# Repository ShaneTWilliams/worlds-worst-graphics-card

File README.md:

# World's Worst Graphics Card

This board consists of an SiI1136 HDMI transmitter, driven by a dual-core 480 MHz STM32H745IIT6 microcontroller, with 64 MB of external SDRAM. It is USB-powered and uses SWD for flash and debug.

The goal of this project is to give me a custom, bare-metal platform on which I can try my hand at implementing simple graphics algorithms from scratch. The STM32 is key for this, with its dual cores, DMA2D (a DMA peripheral designed to fill frame buffers very quickly) and its LTDC peripheral, which will drive the display without any CPU load.

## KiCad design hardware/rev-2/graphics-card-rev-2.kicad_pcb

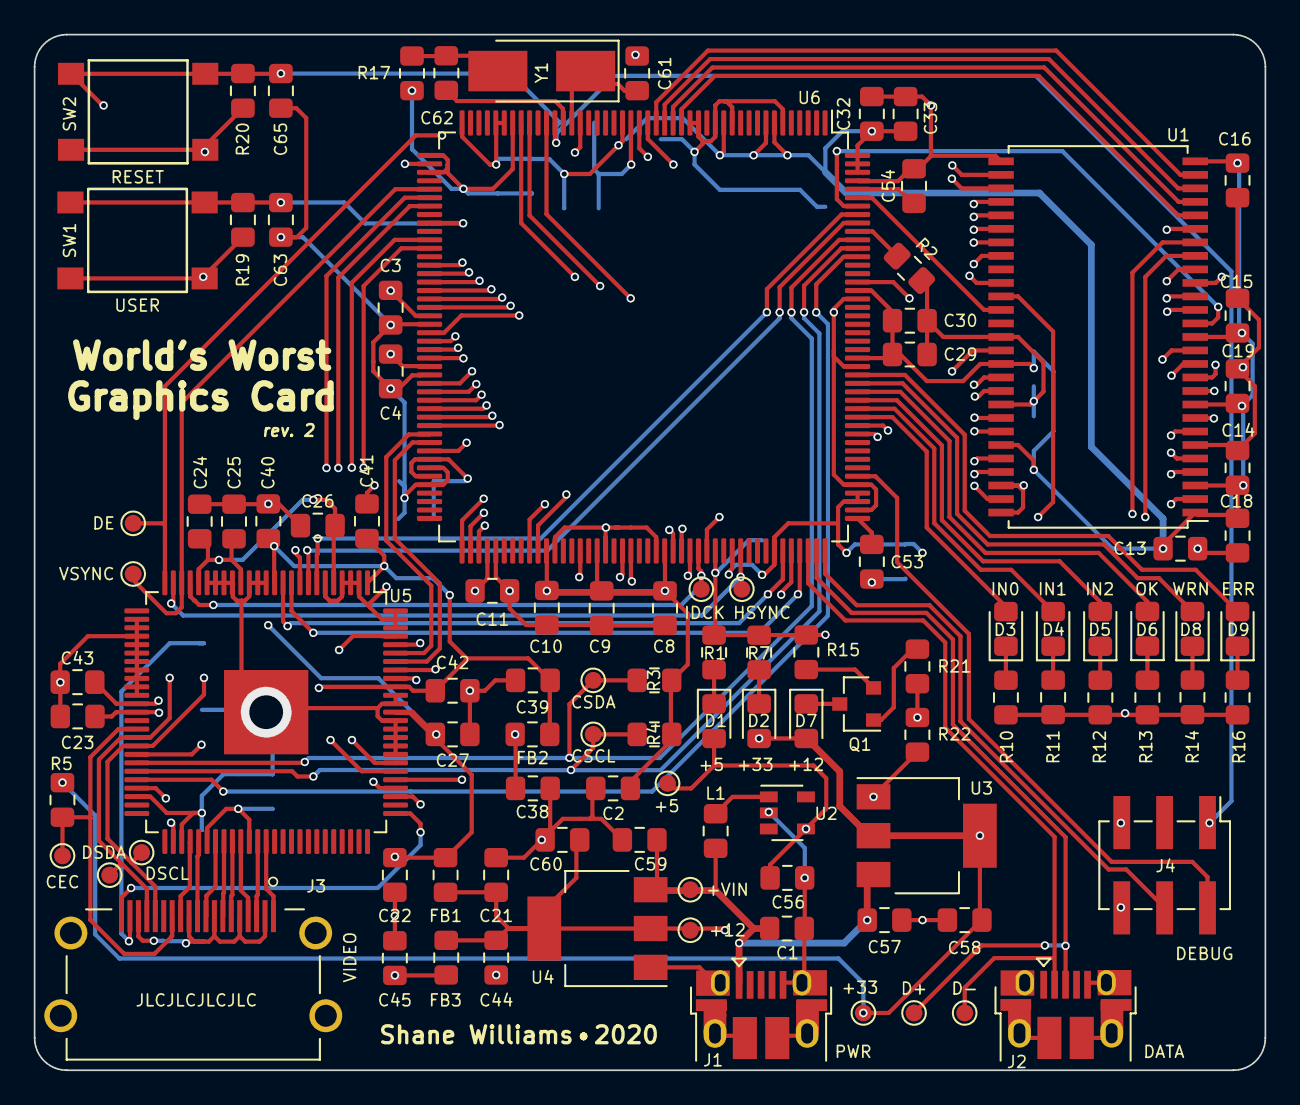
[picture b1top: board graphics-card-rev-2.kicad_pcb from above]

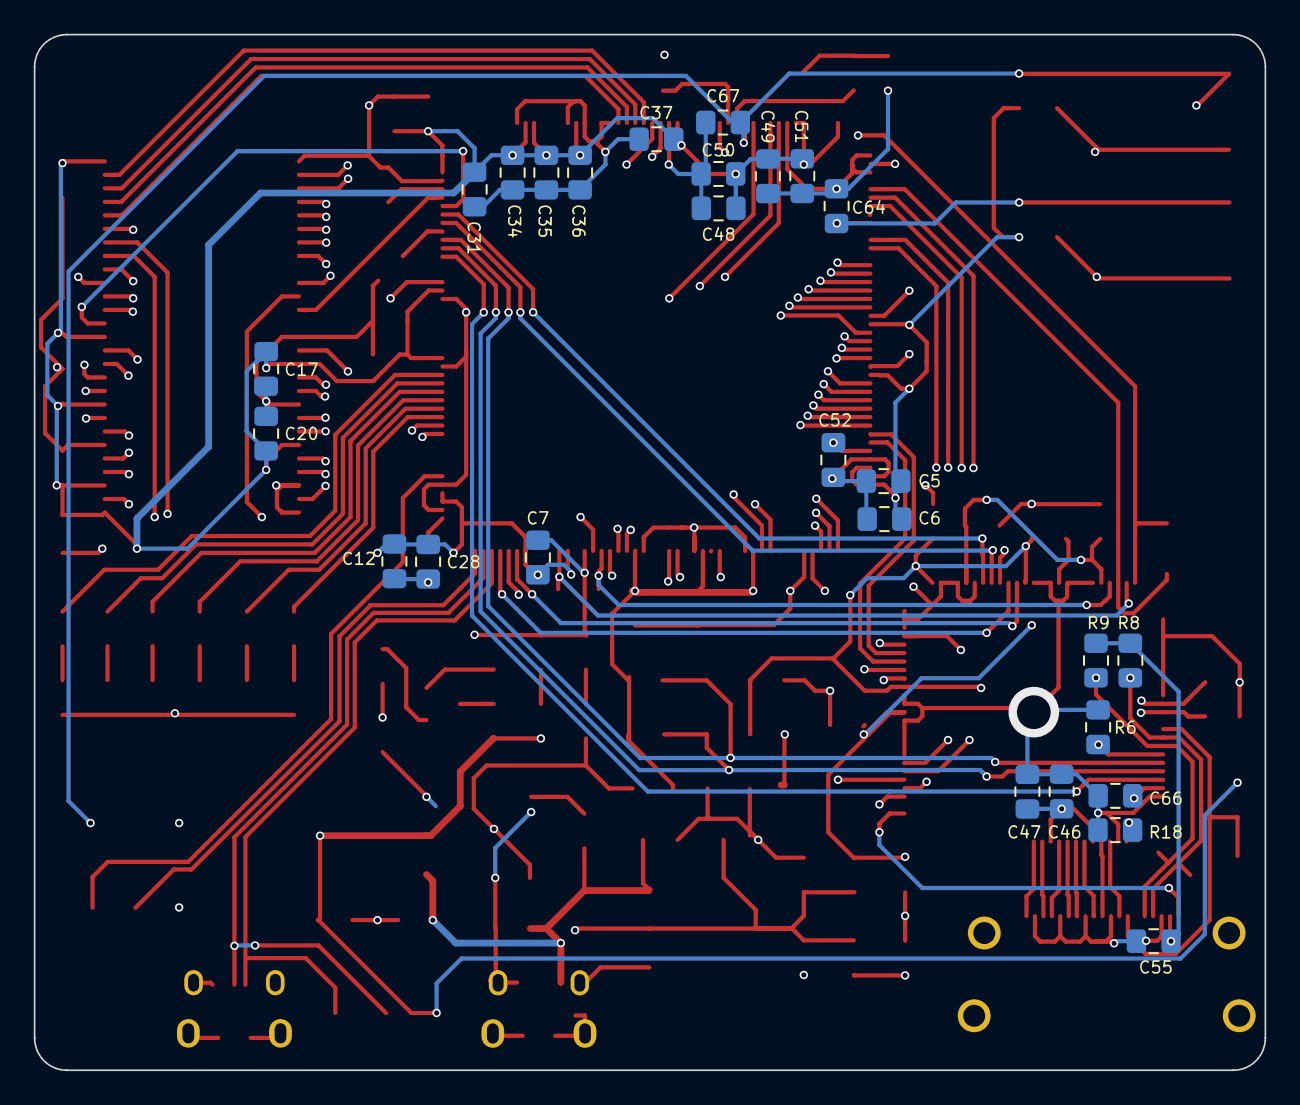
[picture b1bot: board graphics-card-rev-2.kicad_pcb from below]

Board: 4 copper layers, 72.9 x 61.3 mm, 131 parts (27 on the bottom side), 114 nets.

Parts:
+5: +5V; TestPoint_Pad_D1.0mm
+12: +1V2; TestPoint_Pad_D1.0mm
+33: +3V3; TestPoint_Pad_D1.0mm
+VIN: USB_VIN; TestPoint_Pad_D1.0mm
C1, C48, C50: 1u; C_0805_2012Metric_Pad1.15x1.40mm_HandSolder
C2, C13, C57, C58, C59, C60: 4.7u; C_0805_2012Metric_Pad1.15x1.40mm_HandSolder
C3, C4, C5, C6, C7, C8, C9, C10, C11, C12, C14, C15, C16, C17, C18, C19, C20, C21, C23, C24, C25, C26, C27, C28, C29, C30, C31, C32, C33, C34, C35, C36, C37, C38, C40, C41, C42, C43, C44, C46, C47, C49, C51, C55, C63, C64, C65, C66, C67: 100n; C_0805_2012Metric_Pad1.15x1.40mm_HandSolder
C22, C39, C45: 10u; C_0805_2012Metric_Pad1.15x1.40mm_HandSolder
C52, C53, C54: 2.2u; C_0805_2012Metric_Pad1.15x1.40mm_HandSolder
C56: 22u; C_0805_2012Metric_Pad1.15x1.40mm_HandSolder
C61, C62: 10p; C_0805_2012Metric_Pad1.15x1.40mm_HandSolder
CEC: CEC; TestPoint_Pad_D1.0mm
CSCL: CSCL; TestPoint_Pad_D1.0mm
CSDA: CSDA; TestPoint_Pad_D1.0mm
D1: 5V_LED; LED_0805_2012Metric_Pad1.15x1.40mm_HandSolder
D2: 3V3_LED; LED_0805_2012Metric_Pad1.15x1.40mm_HandSolder
D3: LED_IND0; LED_0805_2012Metric_Pad1.15x1.40mm_HandSolder
D4: LED_IND1; LED_0805_2012Metric_Pad1.15x1.40mm_HandSolder
D5: LED_IND2; LED_0805_2012Metric_Pad1.15x1.40mm_HandSolder
D6: LED_OK; LED_0805_2012Metric_Pad1.15x1.40mm_HandSolder
D7: 1V2_LED; LED_0805_2012Metric_Pad1.15x1.40mm_HandSolder
D8: LED_WARN; LED_0805_2012Metric_Pad1.15x1.40mm_HandSolder
D9: LED_ERR; LED_0805_2012Metric_Pad1.15x1.40mm_HandSolder
D+: USB_D+; TestPoint_Pad_D1.0mm
D-: USB_D-; TestPoint_Pad_D1.0mm
DE: DE; TestPoint_Pad_D1.0mm
DSCL: DSCL; TestPoint_Pad_D1.0mm
DSDA: DSDA; TestPoint_Pad_D1.0mm
FB1, FB2, FB3: 1k@100MHz; R_0805_2012Metric_Pad1.15x1.40mm_HandSolder
HSYNC: HSYNC; TestPoint_Pad_D1.0mm
IDCK: IDCK; TestPoint_Pad_D1.0mm
J1, J2: USB_B_Micro; USB_Micro-B_Amphenol_10103594-0001LF_Horizontal
J3: HDMI_A; AMPHENOL_10029449-001RLF
J4: Conn_02x03_Odd_Even; PinHeader_2x03_P2.54mm_Vertical_SMD
L1: 4.7u; L_0805_2012Metric_Pad1.15x1.40mm_HandSolder
Q1: ZXMN2A01F; SOT-23
R1: 510; R_0805_2012Metric_Pad1.15x1.40mm_HandSolder
R2, R19, R20: 10k; R_0805_2012Metric_Pad1.15x1.40mm_HandSolder
R3, R4, R6: 4.7K; R_0805_2012Metric_Pad1.15x1.40mm_HandSolder
R5: 27k; R_0805_2012Metric_Pad1.15x1.40mm_HandSolder
R7, R15: 330; R_0805_2012Metric_Pad1.15x1.40mm_HandSolder
R8, R9: 2k; R_0805_2012Metric_Pad1.15x1.40mm_HandSolder
R10, R11, R12, R13, R14, R16: 680; R_0805_2012Metric_Pad1.15x1.40mm_HandSolder
R17: 400; R_0805_2012Metric_Pad1.15x1.40mm_HandSolder
R18: 4.06k; R_0805_2012Metric_Pad1.15x1.40mm_HandSolder
R21: 100; R_0805_2012Metric_Pad1.15x1.40mm_HandSolder
R22: 1M; R_0805_2012Metric_Pad1.15x1.40mm_HandSolder
SW1, SW2: RESET; PTS645SM43SMTR92_Switch
U1: IS42S16400J-7TL; TSOP-II-54_22.2x10.16mm_P0.8mm
U2: TPS613222ADBVR; SOT-23-5
U3: ZLDO1117G33TA; SOT-223-3_TabPin2
U4: ZLDO1117G12TA; SOT-223-3_TabPin2
U5: SiI1136; TQFP-100-1EP_14x14mm_P0.5mm_EP5x5mm
U6: STM32H745IITx; LQFP-176_24x24mm_P0.5mm
VSYNC: VSYNC; TestPoint_Pad_D1.0mm
Y1: 40MHZ/8PF; Crystal_SMD_5032-2Pin_5.0x3.2mm_HandSoldering

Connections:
+1V2: +12.1, C21.1, C44.1, C60.1, FB1.2, FB3.2, R21.2, R22.1, U4.2
+3V3: +33.1, C2.1, C3.1, C4.1, C5.1, C6.1, C7.1, C8.1, C9.1, C10.1, C11.1, C12.1, C13.1, C14.1, C15.1, C16.1, C17.1, C18.1, C19.1, C20.1, C28.1, C29.1, C30.1, C31.1, C32.1, C33.1, C34.1, C35.1, C36.1, C37.1, C38.1, C48.1, C49.1, C50.1, C51.1, C58.1, D2.2, D7.2, FB2.2, R3.1, R4.1, R5.1, R19.1, R20.1, U1.1, U1.3, U1.9, U1.14, U1.27, U1.43, U1.49, U3.2, U6.7, U6.8, U6.13, U6.25, U6.39, U6.40, U6.44, U6.65, U6.71, U6.82, U6.84, U6.92, U6.99, U6.105, U6.113, U6.121, U6.126, U6.135, U6.136, U6.152, U6.160, U6.174, U6.175, U6.176
+5V: +5.1, C55.1, C56.1, D1.2, J3.18, R8.1, R9.1, U2.4
/AVCC_SII: C45.1, C46.1, C47.1, FB3.1, U5.56, U5.61
/B_CB_3: U5.11, U6.127
/B_CB_4: U5.10, U6.129
/B_CB_5: U5.9, U6.46
/B_CB_6: U5.8, U6.168
/B_CB_7: U5.7, U6.169
/CEC: CEC.1, J3.13, R5.2, U5.40
/CSCL: CSCL.1, R4.2, U5.45, U6.165
/CSDA: CSDA.1, R3.2, U5.44, U6.166
/CVCC12_SII: C22.1, C23.1, C24.1, C25.1, C26.1, C27.1, FB1.1, U5.5, U5.16, U5.21, U5.38, U5.88
/DE: DE.1, U5.25, U6.30
/DSCL: DSCL.1, J3.15, R9.2, U5.42
/DSDA: DSDA.1, J3.16, R8.2, U5.41
/G_Y_2: U5.97, U6.51
/G_Y_3: U5.96, U6.103
/G_Y_4: U5.95, U6.78
/G_Y_5: U5.94, U6.79
/G_Y_6: U5.93, U6.108
/G_Y_7: U5.92, U6.109
/HPD: J3.19, U5.76
/HSYNC: HSYNC.1, U5.24, U6.122
/IDCK: IDCK.1, U5.22, U6.117
/INT_SII: U5.46, U6.164
/IOVCC_SII: C39.1, C40.1, C41.1, C42.1, C43.1, FB2.1, U5.1, U5.12, U5.37, U5.91
/LED_ERR: D9.2, U6.150
/LED_IND0: D3.2, U6.145
/LED_IND1: D4.2, U6.146
/LED_IND2: D5.2, U6.147
/LED_OK: D6.2, U6.148
/LED_WARN: D8.2, U6.149
/OSC_IN: C61.1, U6.31, Y1.1
/OSC_OUT: R17.1, U6.32
/RAM_A0: U1.23, U6.18
/RAM_A1: U1.24, U6.19
/RAM_A2: U1.25, U6.20
/RAM_A3: U1.26, U6.21
/RAM_A4: U1.29, U6.22
/RAM_A5: U1.30, U6.23
/RAM_A6: U1.31, U6.59
/RAM_A7: U1.32, U6.60
/RAM_A8: U1.33, U6.61
/RAM_A9: U1.34, U6.62
/RAM_A10: U1.22, U6.63
/RAM_A11: U1.35, U6.66
/RAM_BA0: U1.20, U6.114
/RAM_BA1: U1.21, U6.115
/RAM_CKE: U1.37, U6.37
/RAM_CLK: U1.38, U6.118
/RAM_D0: U1.2, U6.97
/RAM_D1: U1.4, U6.98
/RAM_D2: U1.5, U6.143
/RAM_D3: U1.7, U6.144
/RAM_D4: U1.8, U6.67
/RAM_D5: U1.10, U6.68
/RAM_D6: U1.11, U6.69
/RAM_D7: U1.13, U6.72
/RAM_D8: U1.42, U6.73
/RAM_D9: U1.44, U6.74
/RAM_D10: U1.45, U6.75
/RAM_D11: U1.47, U6.76
/RAM_D12: U1.48, U6.77
/RAM_D13: U1.50, U6.89
/RAM_D14: U1.51, U6.90
/RAM_D15: U1.53, U6.91
/RAM_NBL0: U1.15, U6.170
/RAM_NBL1: U1.39, U6.171
/R_CR_3: U5.82, U6.55
/R_CR_4: U5.81, U6.50
/R_CR_5: U5.80, U6.128
/R_CR_6: U5.79, U6.56
/R_CR_7: U5.78, U6.116
/SWCLK: J4.2, U6.138
/SWDIO: J4.4, U6.132
/TMDS_CLK+: J3.10, U5.55
/TMDS_CLK-: J3.12, U5.54
/TMDS_D0+: J3.7, U5.58
/TMDS_D0-: J3.9, U5.57
/TMDS_D1+: J3.4, U5.60
/TMDS_D1-: J3.6, U5.59
/TMDS_D2+: J3.1, U5.63
/TMDS_D2-: J3.3, U5.62
/USB_D+: D+.1, J2.3, U6.131
/USB_D-: D-.1, J2.2, U6.130
/USB_VIN: +VIN.1, C1.1, C57.1, C59.1, J1.1, L1.1, U3.3, U4.3
/VSYNC: U5.23, U6.49, VSYNC.1
/~RAM_CAS: U1.17, U6.161
/~RAM_CS: U1.19, U6.36
/~RAM_RAS: U1.18, U6.58
/~RAM_WE: U1.16, U6.34
/~RESET: C65.1, C66.1, C67.1, J4.1, R20.2, SW2.1, U5.47, U6.33
/~USR_BTN: C63.1, C64.1, R19.2, SW1.1, U6.53
GND: C1.2, C2.2, C3.2, C4.2, C5.2, C6.2, C7.2, C8.2, C9.2, C10.2, C11.2, C12.2, C13.2, C14.2, C15.2, C16.2, C17.2, C18.2, C19.2, C20.2, C21.2, C22.2, C23.2, C24.2, C25.2, C26.2, C27.2, C28.2, C29.2, C30.2, C31.2, C32.2, C33.2, C34.2, C35.2, C36.2, C37.2, C38.2, C39.2, C40.2, C41.2, C42.2, C43.2, C44.2, C45.2, C46.2, C47.2, C48.2, C49.2, C50.2, C51.2, C52.2, C53.2, C54.2, C55.2, C56.2, C57.2, C58.2, C59.2, C60.2, C61.2, C62.2, C63.2, C64.2, C65.2, C66.2, C67.2, J1.5, J1.6, J2.5, J2.6, J3.2, J3.5, J3.8, J3.11, J3.17, J3.SH, J4.5, J4.6, R1.2, R2.2, R6.2, R7.2, R10.1, R11.1, R12.1, R13.1, R14.1, R15.2, R16.1, R18.2, R22.2, SW1.2, SW2.2, U1.6, U1.12, U1.28, U1.41, U1.46, U1.52, U1.54, U2.2, U3.1, U4.1, U5.2, U5.3, U5.4, U5.6, U5.13, U5.14, U5.15, U5.17, U5.18, U5.19, U5.20, U5.27, U5.28, U5.29, U5.30, U5.31, U5.32, U5.33, U5.34, U5.35, U5.36, U5.48, U5.53, U5.83, U5.84, U5.85, U5.86, U5.87, U5.89, U5.90, U5.98, U5.99, U5.100, U5.101, U6.6, U6.12, U6.14, U6.16, U6.17, U6.24, U6.38, U6.45, U6.47, U6.64, U6.70, U6.81, U6.83, U6.93, U6.100, U6.106, U6.112, U6.119, U6.134, U6.137, U6.151, U6.159, U6.173
unnamed: C52.1, U6.80
unnamed: C53.1, U6.133
unnamed: C54.1, U6.172
unnamed: C62.1, R17.2, Y1.2
unnamed: D1.1, R1.1
unnamed: D2.1, R7.1
unnamed: D3.1, R10.2
unnamed: D4.1, R11.2
unnamed: D5.1, R12.2
unnamed: D6.1, R13.2
unnamed: D7.1, Q1.3
unnamed: D8.1, R14.2
unnamed: D9.1, R16.2
unnamed: L1.2, U2.1
unnamed: Q1.1, R21.1
unnamed: Q1.2, R15.1
unnamed: R2.1, U6.167
unnamed: R6.1, U5.43
unnamed: R18.1, U5.52

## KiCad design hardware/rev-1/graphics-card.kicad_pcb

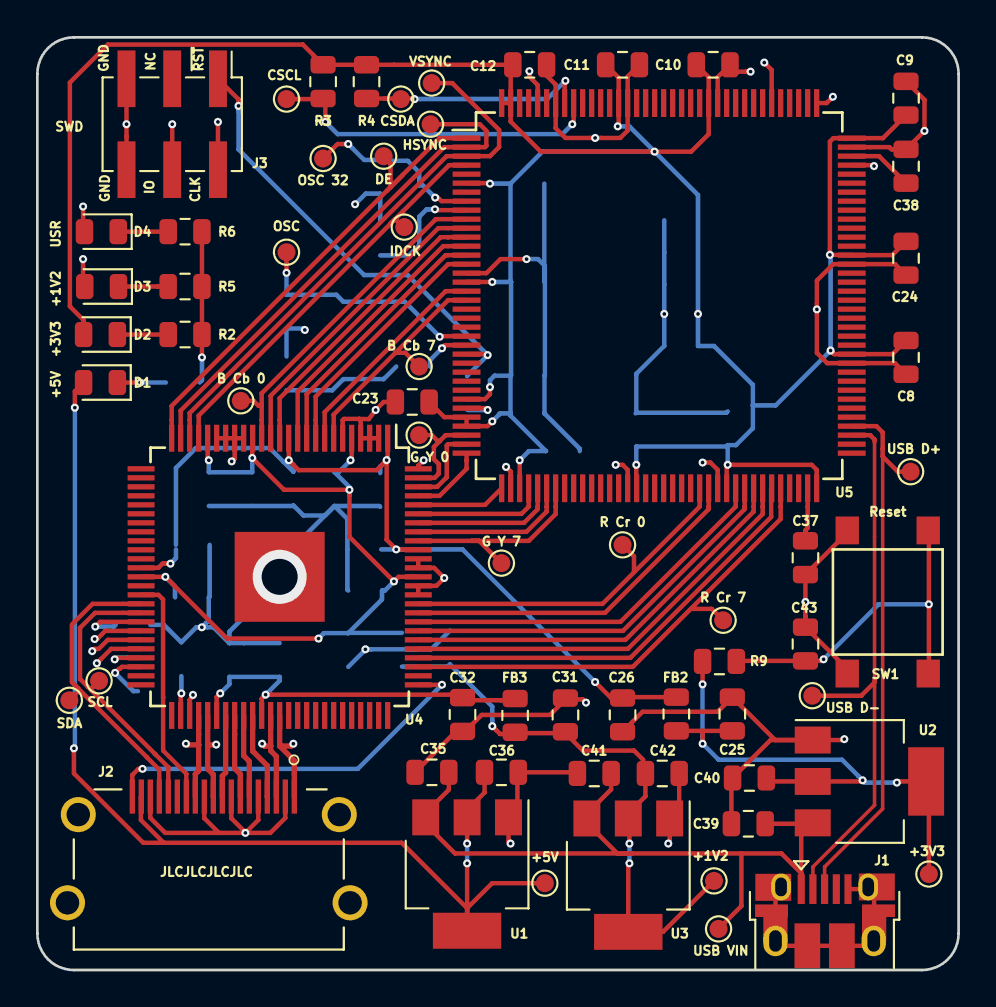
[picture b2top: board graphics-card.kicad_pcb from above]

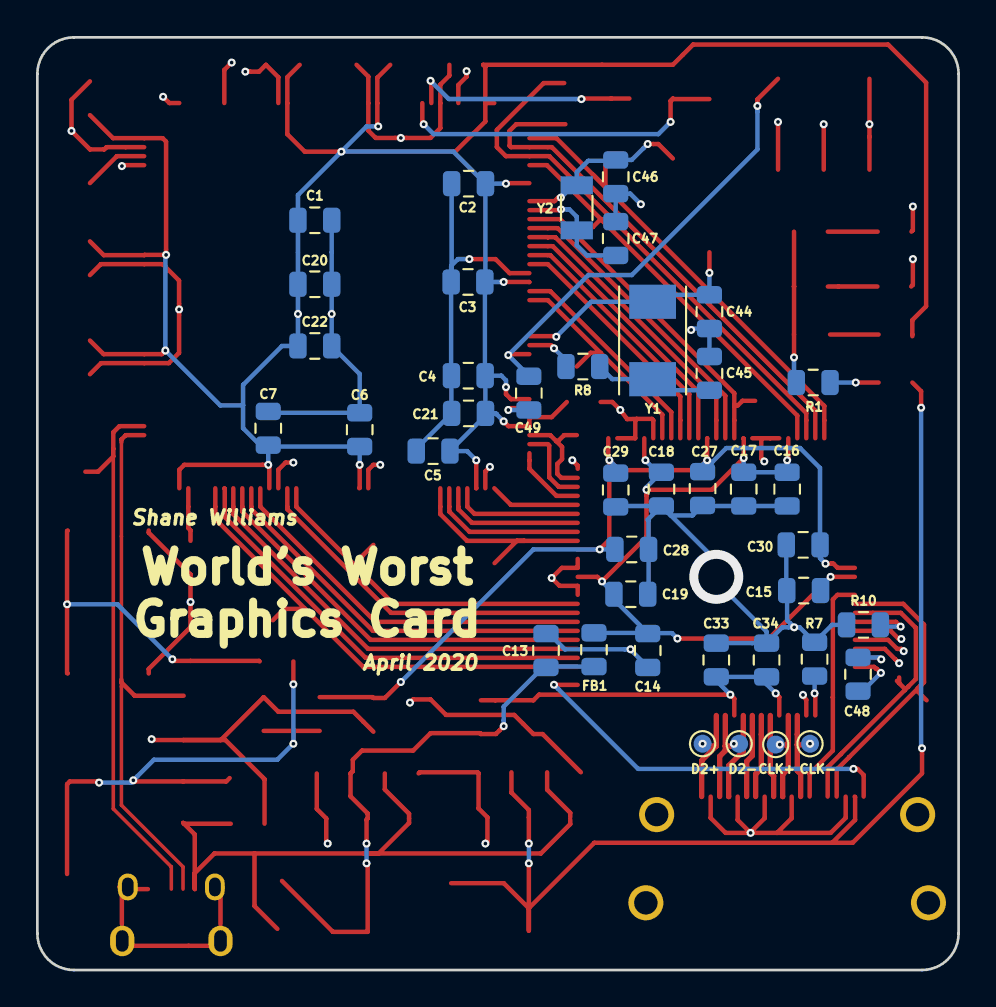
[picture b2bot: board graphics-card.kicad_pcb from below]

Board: 4 copper layers, 51.2 x 51.8 mm, 103 parts (40 on the bottom side), 70 nets.

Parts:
+1V2: +1V2; TestPoint_Pad_D1.0mm
+3V3: +3V3; TestPoint_Pad_D1.0mm
+5V: +5V; TestPoint_Pad_D1.0mm
B Cb 0: B_CB_0; TestPoint_Pad_D1.0mm
B Cb 7: B_CB_7; TestPoint_Pad_D1.0mm
C1: 4.7u; C_0805_2012Metric
C2, C3, C4, C5, C6, C7, C8, C9, C10, C11, C12, C13, C15, C16, C17, C18, C19, C21, C23, C24, C25, C27, C28, C29, C30, C31, C33, C34, C37, C38, C43, C48, C49: 100n; C_0805_2012Metric
C14, C26, C32: 10u; C_0805_2012Metric
C20, C22, C35, C36, C39, C40, C41, C42: 1u; C_0805_2012Metric
C44, C45: 27p; C_0805_2012Metric
C46, C47: 15p; C_0805_2012Metric
CLK+: CLK+; TestPoint_Pad_D1.0mm
CLK-: CLK-; TestPoint_Pad_D1.0mm
CSCL: CSCL; TestPoint_Pad_D1.0mm
CSDA: CSDA; TestPoint_Pad_D1.0mm
D1: 5V Rail LED; LED_0805_2012Metric
D2: 3.3V Rail LED; LED_0805_2012Metric
D2+: D2+; TestPoint_Pad_D1.0mm
D2-: D2-; TestPoint_Pad_D1.0mm
D3: 1.2V Rail LED; LED_0805_2012Metric
D4: USR_LED; LED_0805_2012Metric
DE: DE; TestPoint_Pad_D1.0mm
FB1, FB2, FB3: 1k@100MHz; R_0805_2012Metric
G Y 0: G_Y_0; TestPoint_Pad_D1.0mm
G Y 7: G_Y_7; TestPoint_Pad_D1.0mm
HSYNC: HSYNC; TestPoint_Pad_D1.0mm
IDCK: IDCK; TestPoint_Pad_D1.0mm
J1: USB_B_Micro; USB_Micro-B_Amphenol_10103594-0001LF_Horizontal
J2: HDMI_A_1.4; AMPHENOL_10029449-001RLF
J3: Conn_02x03_Odd_Even; PinHeader_2x03_P2.54mm_Vertical_SMD
OSC: OSC_IN; TestPoint_Pad_D1.0mm
OSC 32: OSC32_IN; TestPoint_Pad_D1.0mm
R1: 510; R_0805_2012Metric
R2: 330; R_0805_2012Metric
R3, R4, R10: 4.7k; R_0805_2012Metric
R5: 120; R_0805_2012Metric
R6: 680; R_0805_2012Metric
R7: 4.06k; R_0805_2012Metric
R8: 240; R_0805_2012Metric
R9: 10k; R_0805_2012Metric
R Cr 0: R_CR_0; TestPoint_Pad_D1.0mm
R Cr 7: R_CR_7; TestPoint_Pad_D1.0mm
SCL: SCL; TestPoint_Pad_D1.0mm
SDA: SDA; TestPoint_Pad_D1.0mm
SW1: Push Switch; PTS645SM43SMTR92_Switch
U1: AZ1117-5.0; SOT-223-3_TabPin2
U2: AZ1117-3.3; SOT-223-3_TabPin2
U3: AZ1117-1.2; SOT-223-3_TabPin2
U4: SiI1136; TQFP-100-1EP_14x14mm_P0.5mm_EP5x5mm
U5: STM32H753ZITx; LQFP-144_20x20mm_P0.5mm
USB D+: USB1_D+; TestPoint_Pad_D1.0mm
USB D-: USB1_D-; TestPoint_Pad_D1.0mm
USB VIN: USB_VIN; TestPoint_Pad_D1.0mm
VSYNC: VSYNC; TestPoint_Pad_D1.0mm
Y1: OSC; Crystal_SMD_Abracon_ABM7-2Pin_6.0x3.5mm
Y2: OSC_32; Crystal_SMD_3215-2Pin_3.2x1.5mm

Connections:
+1V2: +1V2.1, C13.1, C31.1, C42.1, D3.2, FB1.2, FB3.2, U3.2
+3V3: +3V3.1, C1.1, C2.1, C3.1, C4.1, C5.1, C6.1, C7.1, C8.1, C9.1, C10.1, C11.1, C12.1, C20.1, C21.1, C22.1, C23.1, C24.1, C25.1, C40.1, D2.2, FB2.2, R3.1, R4.1, R9.1, U2.2, U5.6, U5.17, U5.30, U5.32, U5.33, U5.39, U5.52, U5.62, U5.72, U5.84, U5.95, U5.108, U5.121, U5.131, U5.143, U5.144
+5V: +5V.1, C36.1, D1.2, J2.18, U1.2
/AVCC_SII: C32.1, C33.1, C34.1, FB3.1, U4.56, U4.61
/B_CB_0: B Cb 0.1, U4.15, U5.10
/B_CB_1: U4.14, U5.11
/B_CB_2: U4.13, U5.12
/B_CB_3: U4.11, U5.13
/B_CB_4: U4.10, U5.14
/B_CB_5: U4.9, U5.15
/B_CB_6: U4.8, U5.18
/B_CB_7: B Cb 7.1, U4.7, U5.19
/CEC: J2.13, U4.40
/CI2CA: R10.2, U4.43
/CLK+: CLK+.1, J2.10, U4.55
/CLK-: CLK-.1, J2.12, U4.54
/CSCL: CSCL.1, R3.2, U4.45, U5.136
/CSDA: CSDA.1, R4.2, U4.44, U5.137
/CVCC12_SII: C14.1, C15.1, C16.1, C17.1, C18.1, C19.1, FB1.1, U4.5, U4.16, U4.21, U4.38, U4.88
/D0+: J2.7, U4.58
/D0-: J2.9, U4.57
/D1+: J2.4, U4.60
/D1-: J2.6, U4.59
/D2+: D2+.1, J2.1, U4.63
/D2-: D2-.1, J2.3, U4.62
/DE: DE.1, U4.25, U5.1
/G_Y_0: G Y 0.1, U4.99, U5.34
/G_Y_1: U4.98, U5.35
/G_Y_2: U4.97, U5.36
/G_Y_3: U4.96, U5.37
/G_Y_4: U4.95, U5.40
/G_Y_5: U4.94, U5.41
/G_Y_6: U4.93, U5.42
/G_Y_7: G Y 7.1, U4.92, U5.43
/HPD: J2.19, U4.76
/HSYNC: HSYNC.1, U4.24, U5.2
/IDCK: IDCK.1, U4.22, U5.4
/INT_SII: U4.46, U5.140
/IOVCC_SII: C26.1, C27.1, C28.1, C29.1, C30.1, FB2.1, U4.1, U4.12, U4.37, U4.91
/OSC32_IN: C46.1, OSC 32.1, U5.8, Y2.1
/OSC32_OUT: C47.1, U5.9, Y2.2
/OSC_IN: C44.1, OSC.1, U5.23, Y1.1
/OSC_OUT: R8.2, U5.24
/R_CR_0: R Cr 0.1, U4.85, U5.59
/R_CR_1: U4.84, U5.60
/R_CR_2: U4.83, U5.63
/R_CR_3: U4.82, U5.64
/R_CR_4: U4.81, U5.65
/R_CR_5: U4.80, U5.66
/R_CR_6: U4.79, U5.67
/R_CR_7: R Cr 7.1, U4.78, U5.68
/SCL: J2.15, SCL.1, U4.42
/SDA: J2.16, SDA.1, U4.41
/SWCLK: J3.2, U5.109
/SWDIO: J3.4, U5.105
/USB1_D+: J1.3, U5.76, USB D+.1
/USB1_D-: J1.2, U5.75, USB D-.1
/USB_VIN: C35.1, C39.1, C41.1, J1.1, U1.3, U2.3, U3.3, USB VIN.1
/VSYNC: U4.23, U5.3, VSYNC.1
/~RESET: C43.1, C48.1, C49.1, J3.1, R9.2, SW1.2, U4.47, U5.25
GND: C1.2, C2.2, C3.2, C4.2, C5.2, C6.2, C7.2, C8.2, C9.2, C10.2, C11.2, C12.2, C13.2, C14.2, C15.2, C16.2, C17.2, C18.2, C19.2, C20.2, C21.2, C22.2, C23.2, C24.2, C25.2, C26.2, C27.2, C28.2, C29.2, C30.2, C31.2, C32.2, C33.2, C34.2, C35.2, C36.2, C37.2, C38.2, C39.2, C40.2, C41.2, C42.2, C43.2, C44.2, C45.2, C46.2, C47.2, C48.2, C49.2, J1.5, J1.6, J2.2, J2.5, J2.8, J2.11, J2.17, J2.SH, J3.5, J3.6, R1.2, R2.2, R5.2, R6.1, R7.2, R10.1, SW1.1, U1.1, U2.1, U3.1, U4.2, U4.3, U4.4, U4.6, U4.17, U4.18, U4.19, U4.20, U4.48, U4.53, U4.86, U4.87, U4.89, U4.90, U4.100, U4.101, U5.16, U5.31, U5.38, U5.51, U5.61, U5.83, U5.94, U5.107, U5.120, U5.130, U5.138
unnamed: C37.1, U5.71
unnamed: C38.1, U5.106
unnamed: C45.1, R8.1, Y1.2
unnamed: D1.1, R1.1
unnamed: D2.1, R2.1
unnamed: D3.1, R5.1
unnamed: D4.1, R6.2
unnamed: D4.2, U5.114
unnamed: R7.1, U4.52

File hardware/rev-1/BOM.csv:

"Id";"Designator";"Package";"Quantity";"Designation";"Supplier and ref";
1;"J2";"AMPHENOL_10029449-001RLF";1;"HDMI_A_1.4";;;
2;"CLK+";"TestPoint_Pad_D1.0mm";1;"CLK+";;;
3;"U5";"LQFP-144_20x20mm_P0.5mm";1;"STM32H753ZITx";;;
4;"C20,C22,C35,C36,C39,C40,C41,C42";"C_0805_2012Metric";8;"1u";;;
5;"C44,C45";"C_0805_2012Metric";2;"27p";;;
6;"C46,C47";"C_0805_2012Metric";2;"15p";;;
7;"R8";"R_0805_2012Metric";1;"240";;;
8;"Y1";"Crystal_SMD_Abracon_ABM7-2Pin_6.0x3.5mm";1;"OSC";;;
9;"Y2";"Crystal_SMD_3215-2Pin_3.2x1.5mm";1;"OSC_32";;;
10;"C1";"C_0805_2012Metric";1;"4.7u";;;
11;"C2,C3,C4,C5,C6,C7,C8,C9,C10,C11,C12,C13,C15,C16,C17,C18,C19,C21,C23,C24,C25,C27,C28,C29,C30,C31,C33,C34,C37,C38,C43,C48,C49";"C_0805_2012Metric";33;"100n";;;
12;"C14,C26,C32";"C_0805_2012Metric";3;"10u";;;
13;"D1";"LED_0805_2012Metric";1;"5V Rail LED";;;
14;"D2";"LED_0805_2012Metric";1;"3.3V Rail LED";;;
15;"D3";"LED_0805_2012Metric";1;"1.2V Rail LED";;;
16;"D4";"LED_0805_2012Metric";1;"USR_LED";;;
17;"FB1,FB2,FB3";"R_0805_2012Metric";3;"1k@100MHz";;;
18;"R1";"R_0805_2012Metric";1;"510";;;
19;"R2";"R_0805_2012Metric";1;"330";;;
20;"R3,R4,R10";"R_0805_2012Metric";3;"4.7k";;;
21;"R5";"R_0805_2012Metric";1;"120";;;
22;"R6";"R_0805_2012Metric";1;"680";;;
23;"R7";"R_0805_2012Metric";1;"4.06k";;;
24;"SW1";"PTS645SM43SMTR92_Switch";1;"Push Switch";;;
25;"U1";"SOT-223-3_TabPin2";1;"AZ1117-5.0";;;
26;"U2";"SOT-223-3_TabPin2";1;"AZ1117-3.3";;;
27;"U3";"SOT-223-3_TabPin2";1;"AZ1117-1.2";;;
28;"J1";"USB_Micro-B_Amphenol_10103594-0001LF_Horizontal";1;"USB_B_Micro";;;
29;"J3";"PinHeader_2x03_P2.54mm_Vertical_SMD";1;"Conn_02x03_Odd_Even";;;
30;"USB VIN";"TestPoint_Pad_D1.0mm";1;"USB_VIN";;;
31;"USB D+";"TestPoint_Pad_D1.0mm";1;"USB1_D+";;;
32;"USB D-";"TestPoint_Pad_D1.0mm";1;"USB1_D-";;;
33;"+5V";"TestPoint_Pad_D1.0mm";1;"+5V";;;
34;"+3V3";"TestPoint_Pad_D1.0mm";1;"+3V3";;;
35;"R Cr 7";"TestPoint_Pad_D1.0mm";1;"R_CR_7";;;
36;"+1V2";"TestPoint_Pad_D1.0mm";1;"+1V2";;;
37;"CSCL";"TestPoint_Pad_D1.0mm";1;"CSCL";;;
38;"CSDA";"TestPoint_Pad_D1.0mm";1;"CSDA";;;
39;"R Cr 0";"TestPoint_Pad_D1.0mm";1;"R_CR_0";;;
40;"G Y 7";"TestPoint_Pad_D1.0mm";1;"G_Y_7";;;
41;"G Y 0";"TestPoint_Pad_D1.0mm";1;"G_Y_0";;;
42;"B Cb 7";"TestPoint_Pad_D1.0mm";1;"B_CB_7";;;
43;"OSC";"TestPoint_Pad_D1.0mm";1;"OSC_IN";;;
44;"B Cb 0";"TestPoint_Pad_D1.0mm";1;"B_CB_0";;;
45;"OSC 32";"TestPoint_Pad_D1.0mm";1;"OSC32_IN";;;
46;"D2+";"TestPoint_Pad_D1.0mm";1;"D2+";;;
47;"D2-";"TestPoint_Pad_D1.0mm";1;"D2-";;;
48;"CLK-";"TestPoint_Pad_D1.0mm";1;"CLK-";;;
49;"SCL";"TestPoint_Pad_D1.0mm";1;"SCL";;;
50;"SDA";"TestPoint_Pad_D1.0mm";1;"SDA";;;
51;"DE";"TestPoint_Pad_D1.0mm";1;"DE";;;
52;"HSYNC";"TestPoint_Pad_D1.0mm";1;"HSYNC";;;
53;"VSYNC";"TestPoint_Pad_D1.0mm";1;"VSYNC";;;
54;"IDCK";"TestPoint_Pad_D1.0mm";1;"IDCK";;;
55;"U4";"TQFP-100-1EP_14x14mm_P0.5mm_EP5x5mm";1;"SiI1136";;;
56;"R9";"R_0805_2012Metric";1;"10k";;;

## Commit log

2020-08-05 style: Add .gitignore
2020-08-05 feat: Add first revision hardware files
2020-08-05 feat: Add STM32CubeIDE project with boilerplate HAL code
2020-09-03 [WIP] feat: Add EDID parsing library
2020-12-20 feat: Add second revision hardware files
2021-01-02 Update README.md with information about second hardware revision
2021-01-02 [WIP] feat: Add SiI1136 driver
